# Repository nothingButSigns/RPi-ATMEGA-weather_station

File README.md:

# RPi-ATMEGA weather station
Project of weather station involving RPi, AVR microcontroller ATMEGA329P and radio transmission

The project concerns electronical and programming aspect of weather station.
The station itself is based on AVR microcontroller - ATMEGA 328p and set of sensors which allow to collect following data:
* temperature [°C]
* humidity [%RH]
* pressure [hPa]
* luminosity [lux]
* wind direction and wind speed [m/s]

The data is read every 1 h and sent via nRF24L01+PA radio tranceiver to Raspberry Pi 3B+ and saved in mysql database.

The repository contains eagle project of PCB board (THT) for the station and schematic. Libraries of parts which could not be found in EAGLE are included.

The project requires mySQL database to be installed on RPi.
MySQL database schema can be then imported with following terminal command:
```sh
$ mysql -u root -p [DB_NAME] < \path\user_name\Downloads\file.sql
```

C program (meteo_station.ino) was written in Arduino IDE 1.8.9.
Arduino bootloader was uploaded to ATMEGA 328P as instructed by [Nick Gammon](http://www.gammon.com.au/forum/?id=11637).
Following libraries are necessary:
* [Adafruit Sensor](https://github.com/adafruit/Adafruit_Sensor)
* [Wire](https://github.com/esp8266/Arduino/tree/master/libraries/Wire)
* [Adafruit BME280](https://github.com/adafruit/Adafruit_BME280_Library)
* [BH1750](https://github.com/claws/BH1750)
* [RF24](http://tmrh20.github.io/RF24)

C++ program written for RPi requires [RF24 library](https://github.com/nRF24/RF24) which contains essential dependencies (WiringPi & BCM2835) and [mySQL-cpp-connector] (https://dev.mysql.com/downloads/connector/cpp/)

The station is powered with 3.7 V NCR18650B connected to circuit via JACK socket. The battery is not included in schematic.

#BOM
| Q-ty | Part name | Value | Package | Description |
| --- | --------- | ----- | ------- | ----------- |
|1|ATMEGA328P|-|DIP|AVR Microcontroller|
|1|WIRELESS-NRF24L01-PA-EXT|-|-|2.4 GHz Wireless Module based on NRF24L01|
|1|BME280|-|-|Digital Humidity-Temperature-Pressure Sensor|
|1|BH1750|-|-|Digital Light Sensor|
|1|Lacrosse TX20|-|-|Wind speed and direction sensor|
|1|Quartz Crystal|8MHz|HC49/S|-|
|2|Electrolytic capacitor|0.1 uF|C2.5-3|-|
|1|Electrolytic capacitor|0.22 uF|C2.5-3|-|
|1|Electrolytic capacitor|4.7 uF|C2.5-3|-|
|2|Ceramic capacitor|22 pF|C2.5-3|-|
|3|Resistor|0 Ω |0204/5|-|
|1|Resistor|10 kΩ|0204/5|-|
|1|LFXXCVS|LF33CVS|TO220 S|Voltage regulator|
|1|JACK-PLUG|-|SPC4077|Plug to enable circuit powering with DC|
|1|4-pin terminal block|3.5 mm|-|Terminal block with round pad|

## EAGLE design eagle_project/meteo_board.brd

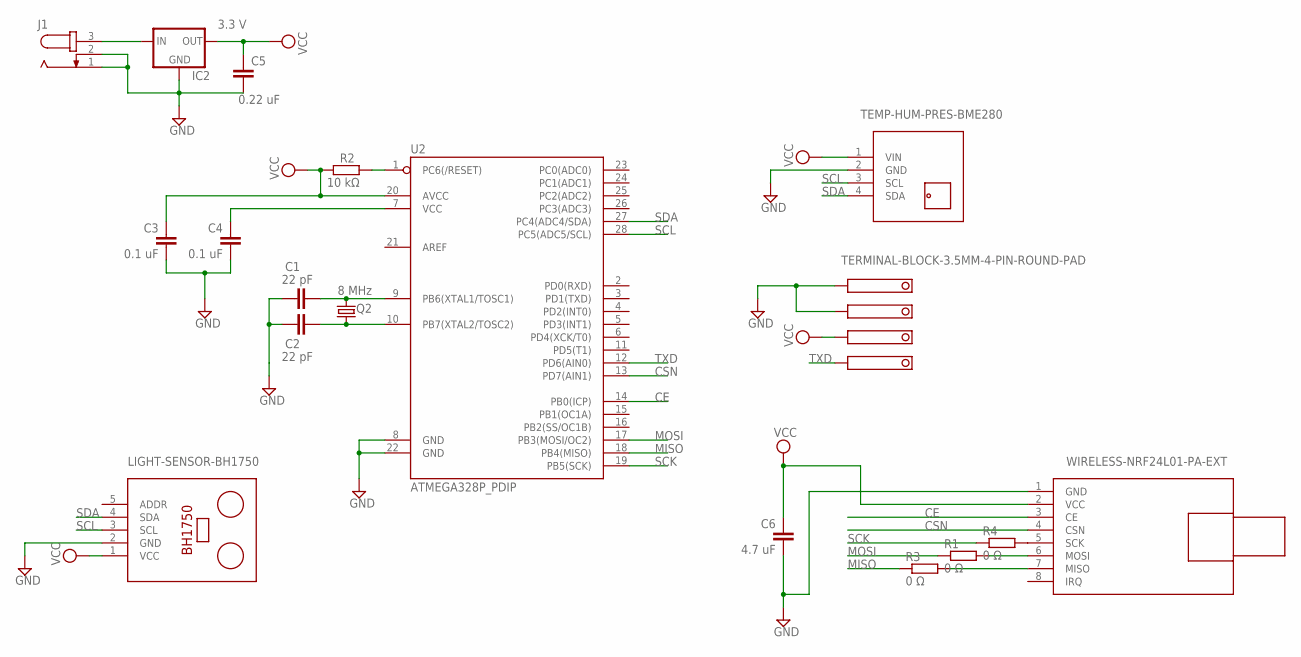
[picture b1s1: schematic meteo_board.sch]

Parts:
C1, C2: 22 pF; C2.5-3
C3, C4: 0.1 uF; C2.5-3
C5: 0.22 uF; C2.5-3
C6: 4.7 uF; C2.5-3
IC2: LFXXCVS; TO220S
J1: JACK-PLUG0; SPC4077
M1: WIRELESS-NRF24L01-PA-EXT
Q2: 8 MHz; HC49/S
R1, R3, R4: 0 Ω; 0204/5
R2: 10 kΩ; 0204/5
TX20: TERMINAL-BLOCK-3.5MM-4-PIN-ROUND-PAD; TERMINAL-BLOCK-4-PIN-3.5MM-ROUND-PAD
U2: ATMEGA328P_PDIP; DIL28-3
U$5: LIGHT-SENSOR-BH1750
U$6: TEMP-HUM-PRES-BME280

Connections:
CE: M1.3 (CE), U2.14 (PB0(ICP))
CSN: M1.4 (CSN), U2.13 (PD7(AIN1))
GND: C1.1, C2.1, C3.1, C4.1, C5.2, C6.1, IC2.2 (GND), J1.1, J1.2, M1.1 (GND), TX20.1, TX20.2, U2.8 (GND), U2.22 (GND), U$5.2 (GND), U$6.2 (GND)
MISO: R3.1, U2.18 (PB4(MISO))
MOSI: R1.1, U2.17 (PB3(MOSI/OC2))
unnamed: IC2.1 (IN), J1.3
unnamed: R2.2, U2.1 (PC6(/RESET))
unnamed: M1.5 (SCK), R4.2
unnamed: C1.2, Q2.2, U2.9 (PB6(XTAL1/TOSC1))
unnamed: C2.2, Q2.1, U2.10 (PB7(XTAL2/TOSC2))
unnamed: M1.6 (MOSI), R1.2
unnamed: M1.7 (MISO), R3.2
unnamed: C4.2, U2.7 (VCC)
SCK: R4.1, U2.19 (PB5(SCK))
SCL: U2.28 (PC5(ADC5/SCL)), U$5.3 (SCL), U$6.3 (SCL)
SDA: U2.27 (PC4(ADC4/SDA)), U$5.4 (SDA), U$6.4 (SDA)
TXD: TX20.4, U2.12 (PD6(AIN0))
VCC: C3.2, C5.1, C6.2, IC2.3 (OUT), M1.2 (VCC), R2.1, TX20.3, U2.20 (AVCC), U$5.1 (VCC), U$6.1 (VIN)

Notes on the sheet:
3.3 V

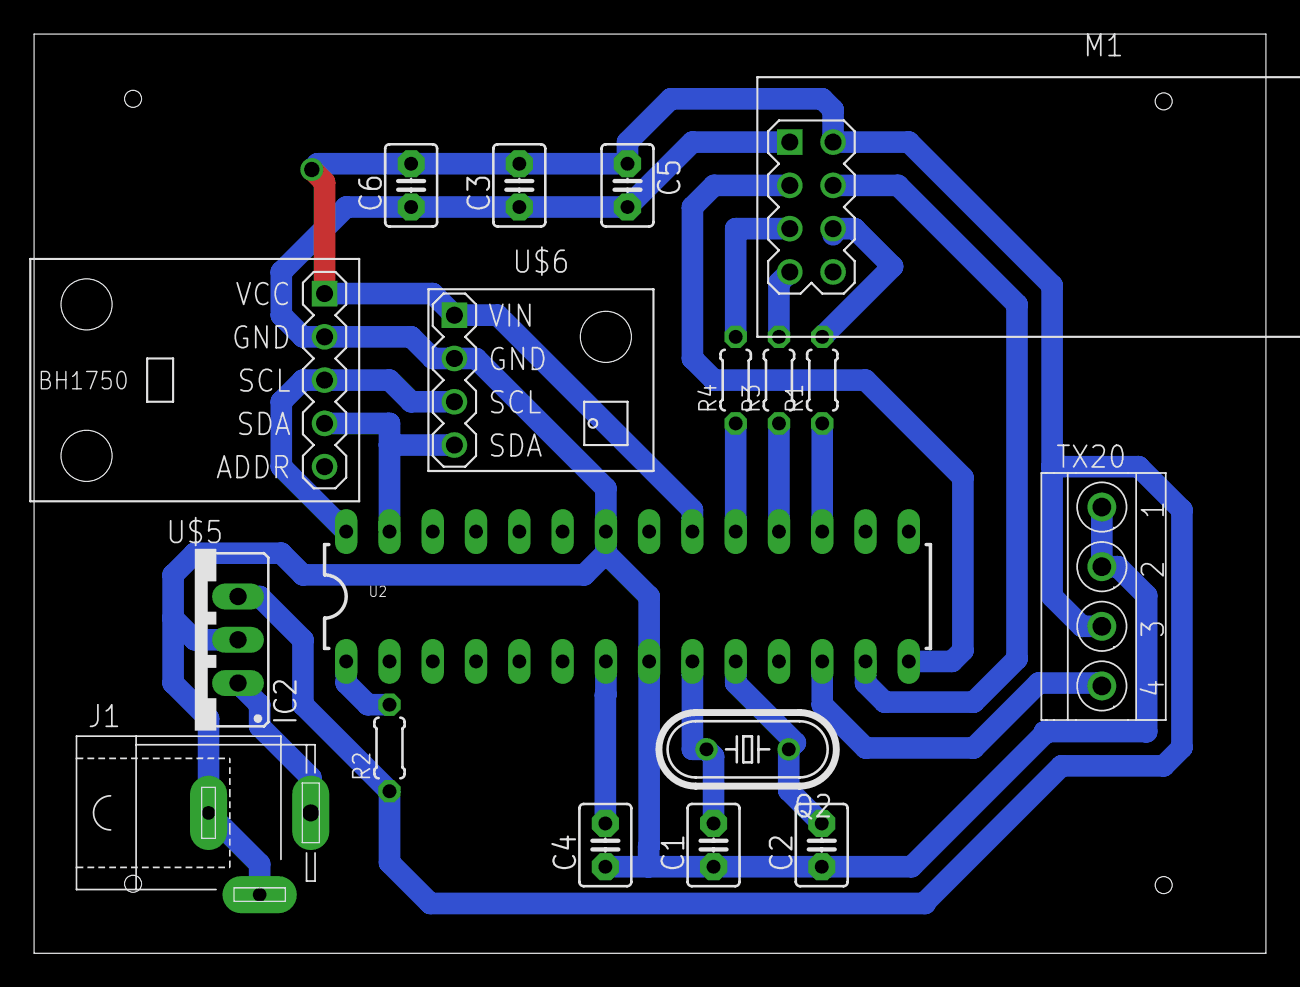
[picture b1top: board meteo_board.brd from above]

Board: 2 copper layers, 72.3 x 54.0 mm, 18 parts (0 on the bottom side), 18 nets.

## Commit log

2020-08-03 README files added
2020-08-03 Edit README.md
2020-08-03 Move .ino sketch to separate folder

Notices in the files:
parts and their libraries:
diy-modules: Released under the Creative Commons Attribution 4.0 International License: http://creativecommons.org/licenses/by/4.0
